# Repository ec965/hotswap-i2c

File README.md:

# Hotswap I2C breakout board

This board uses the TCA4311ADR by Texas Instruments. More information can be found in the data sheet.

## Wiring Example

```
       5V+ -> VCC                 VCC -> 5V+ 
Master SDA -> SDAIN  TCA4311A  SDAOUT -> Slave SDA
Master SCL -> SCLIN            SCLOUT -> Slave SCL
       GND -> GND                 GND -> GND
```

Pullup resistors are required on both sides on the I2C bus.

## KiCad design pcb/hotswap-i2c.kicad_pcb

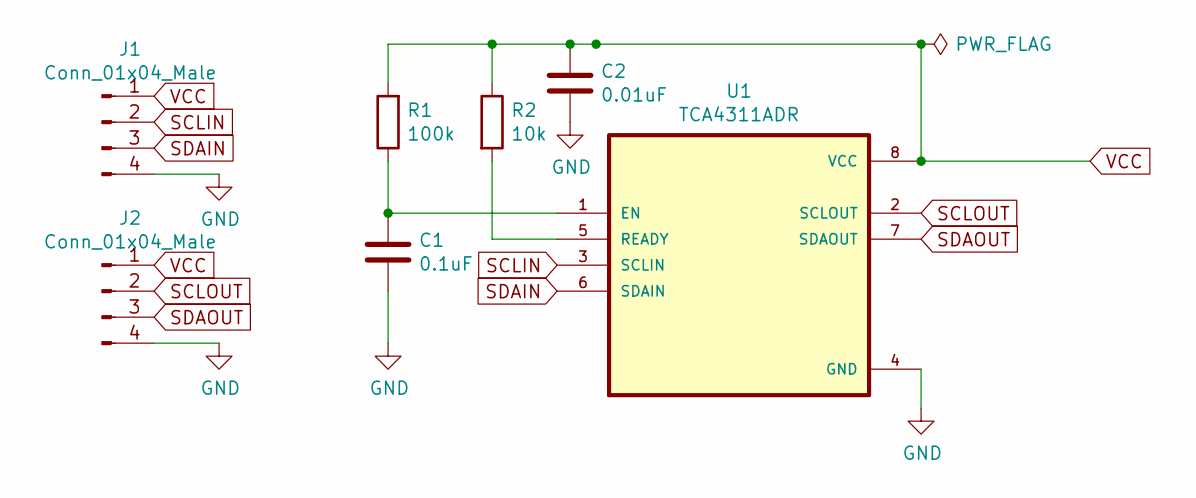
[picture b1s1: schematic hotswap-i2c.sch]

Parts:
C1: 0.1uF; C_0603_1608Metric_Pad1.05x0.95mm_HandSolder
C2: 0.01uF; C_0603_1608Metric_Pad1.05x0.95mm_HandSolder
J1, J2: Conn_01x04_Male; PinHeader_1x04_P2.54mm_Vertical
R1: 100k; R_0603_1608Metric_Pad0.98x0.95mm_HandSolder
R2: 10k; R_0603_1608Metric_Pad0.98x0.95mm_HandSolder
U1: TCA4311ADR; SOIC127P599X175-8N

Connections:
GND: C1.2, C2.2, J1.4, J2.4, U1.4 (GND)
unnamed: C1.1, R1.1, U1.1 (EN)
unnamed: R2.2, U1.5 (READY)
SCLIN: J1.2, U1.3 (SCLIN)
SCLOUT: J2.2, U1.2 (SCLOUT)
SDAIN: J1.3, U1.6 (SDAIN)
SDAOUT: J2.3, U1.7 (SDAOUT)
VCC: C2.1, J1.1, J2.1, R1.2, R2.1, U1.8 (VCC)

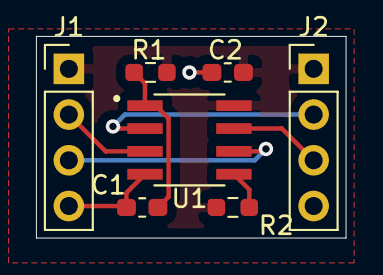
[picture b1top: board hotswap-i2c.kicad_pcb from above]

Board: 2 copper layers, 17.2 x 11.2 mm, 7 parts (0 on the bottom side), 8 nets.

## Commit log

2020-12-14 init
2020-12-14 add decoupling cap
2020-12-14 some rerouting
2020-12-14 update design, add license
2020-12-14 update image
